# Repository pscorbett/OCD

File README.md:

# Over-Complicated Distortion (OCD)

This is a highly tweakable distortion pedal based around soft-clipping diodes in feedback.

## Controls
1. **Drive:** Adds gain to push the diodes into their non-linear region.
2. **Filter:** Crossmixes between Lowpass Filter and Highpass Filter. The 2nd-order Salley-key filter occurs before the clipping stage.
3. **Bias:** Adds a DC shift to the signal prior to the clipping stage. This can be used for asymmetric clipping as would occur in many tube and transistor Class-A amplifiers if they exceed their linear range.
4. **Symmetry:** Blends betweent the forward and reverse steering diodes in the feedback path. At higher gain values, the asymmetry will be diminished as the second set of (symmetric) clipping diodes is mixed in. This is done to achieve more extreme waveshaping than is possible with the resistance from the potentiometer limitng the steering current.
5. **Attenuvert:** This acts as an ouput control that affects only the clipped signal. In the CCW direction, the signal inverts.
6. **Mix:** Mixes between the dry and wet (distorted) signals. High distortion settings with low mix can simulate the crossover distortion produced by a Class B push-pull amplifier. Reversing the polarity results in a different flavor of crossover distortion.

Despite the name, this circuit has no association or deliberate simularities with other *OCD* distortion pedals.

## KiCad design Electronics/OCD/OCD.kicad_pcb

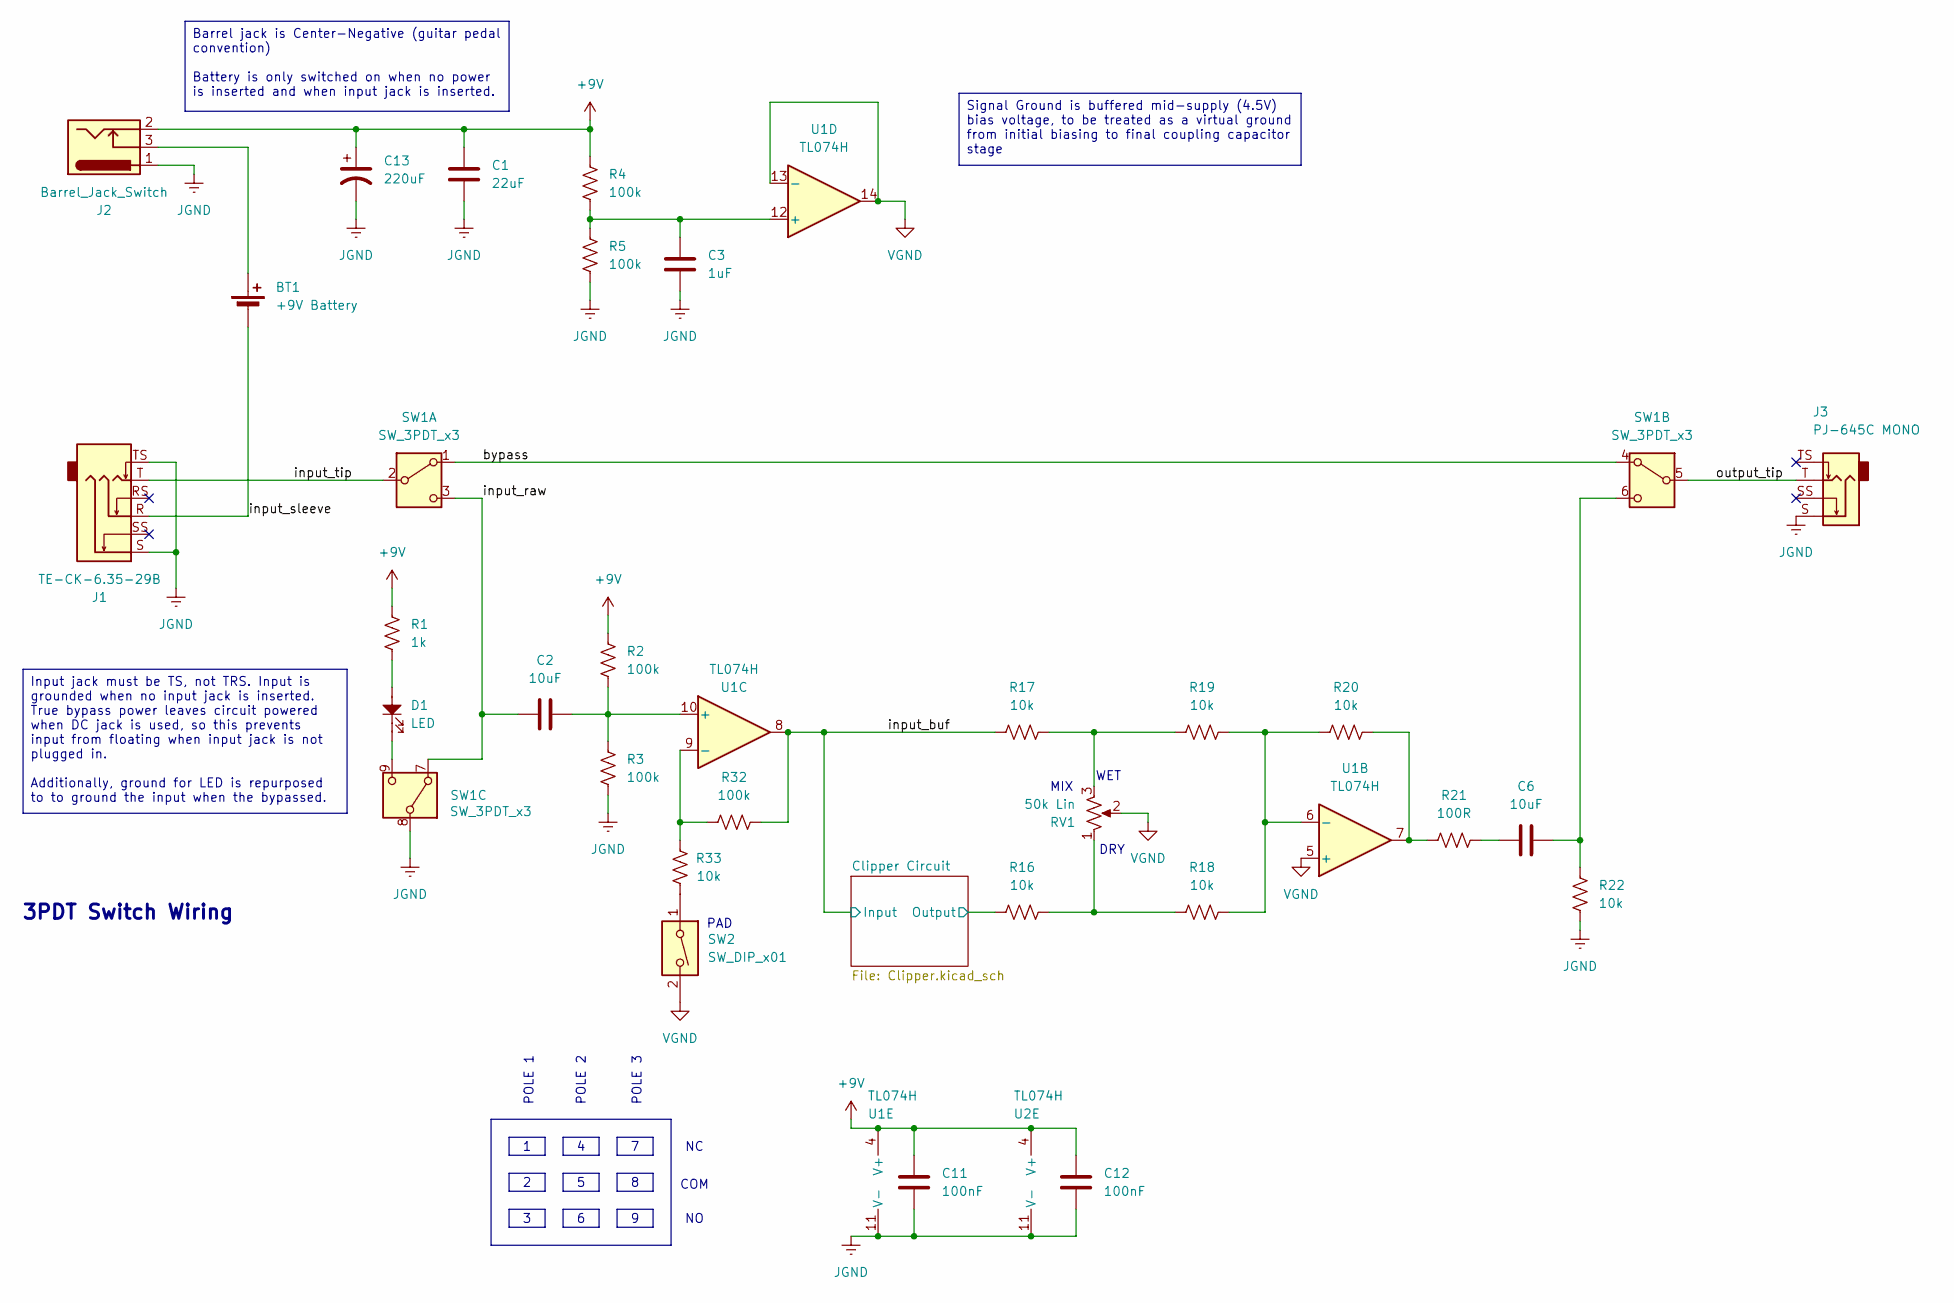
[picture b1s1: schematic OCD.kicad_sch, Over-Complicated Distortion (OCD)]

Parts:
BT1: +9V Battery; PinHeader_1x02_P2.54mm_Vertical; Part Number BH9VPC
C1: 22uF; C_0805_2012Metric; Part Number CL21A226MAQNNNE
C2, C6: 10uF; C_0805_2012Metric; Part Number GRM21BZ71E106KE15L
C3: 1uF; C_0805_2012Metric; Part Number CL21B105KBFNNNE
C11, C12: 100nF; C_0805_2012Metric; Part Number CL21B104KCFNNNE
C13: 220uF; CP_Elec_8x10; Part Number UUD1E221MNL1GS
D1: LED; LED_D5.0mm; Part Number PBS-24-302-N2 Red/Green LED
J1: TE-CK-6.35-29B; Part Number TE-PJ-645C
J2: Barrel_Jack_Switch; PinHeader_1x03_P2.54mm_Vertical; Part Number DC Power Bulkhead Jack 2.1mm
J3: PJ-645C MONO; PJ-644C MONO; Part Number PJ-645C MONO
R1: 1k; R_0805_2012Metric; Part Number 0805W8F1001T5E
R2, R3, R4, R5, R32: 100k; R_0805_2012Metric; Part Number 0805W8F1003T5E
R16, R17, R18, R19, R20, R22, R33: 10k; R_0805_2012Metric; Part Number 0805W8F1002T5E
R21: 100R; R_0805_2012Metric; Part Number 0805W8F1000T5E
RV1: 50k Lin; RV16AF-41; Part Number RV16106NO-OS15A00-B50K-060C
SW1: SW_3PDT_x3; PinHeader_1x09_P2.54mm_Vertical; Part Number PBS-24-302-N2 Red/Green LED
SW2: SW_DIP_x01; SW_DIP_SPSTx01_Slide_6.7x4.1mm_W8.61mm_P2.54mm_LowProfile; Part Number DSIC01LSGET
U1, U2: TL074H; SOIC-14_3.9x8.7mm_P1.27mm; Part Number TL074HIDR

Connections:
+9V: C1.1, C11.2, C12.2, C13.1, J2.2, R1.1, R2.1, R4.1, U1.4 (V+), U2.4 (V+); also elsewhere on the board
/Clipper Circuit/Output: R16.1; also elsewhere on the board
/bypass: SW1.1 (A), SW1.4 (A)
/input_buf: R17.1, R32.2, U1.8; also elsewhere on the board
/input_raw: C2.1, SW1.3 (C), SW1.7 (A)
/input_sleeve: BT1.2 (-), J1.R
/input_tip: J1.T, SW1.2 (B)
/output_tip: J3.T, SW1.5 (B)
JGND: C1.2, C3.2, C11.1, C12.1, C13.2, J1.S, J1.TS, J2.1, J3.S, R3.2, R5.2, R22.1, SW1.8 (B), U1.11 (V-), U2.11 (V-); also elsewhere on the board
unnamed: BT1.1 (+), J2.3
unnamed: C6.1, R21.2
unnamed: D1.2, R1.2
unnamed: R16.2, R18.1, RV1.1
unnamed: R17.2, R19.1, RV1.3
unnamed: R20.2, R21.1, U1.7
unnamed: R33.2, SW2.1
unnamed: C6.2, R22.2, SW1.6 (C)
unnamed: D1.1, SW1.9 (C)
unnamed: R18.2, R19.2, R20.1, U1.6 (-)
unnamed: C2.2, R2.2, R3.1, U1.10 (+)
unnamed: R32.1, R33.1, U1.9 (-)
unnamed: C3.1, R4.2, R5.1, U1.12 (+)
VGND: RV1.2, SW2.2, U1.5 (+), U1.13 (-), U1.14; also elsewhere on the board

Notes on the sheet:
PAD
POLE 1
COM
3PDT Switch Wiring
WET
DRY
MIX
POLE 2
POLE 3
Signal Ground is buffered mid-supply (4.5V) bias voltage, to be treated as a virtual ground from initial biasing to final coupling capacitor stage
Barrel jack is Center-Negative (guitar pedal convention) Battery is only switched on when no power is inserted and when input jack is inserted.
Input jack must be TS, not TRS. Input is grounded when no input jack is inserted. True bypass power leaves circuit powered when DC jack is used, so this prevents input from floating when input jack is not plugged in. Additionally, ground for LED is repurposed to to ground the input when the bypasse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

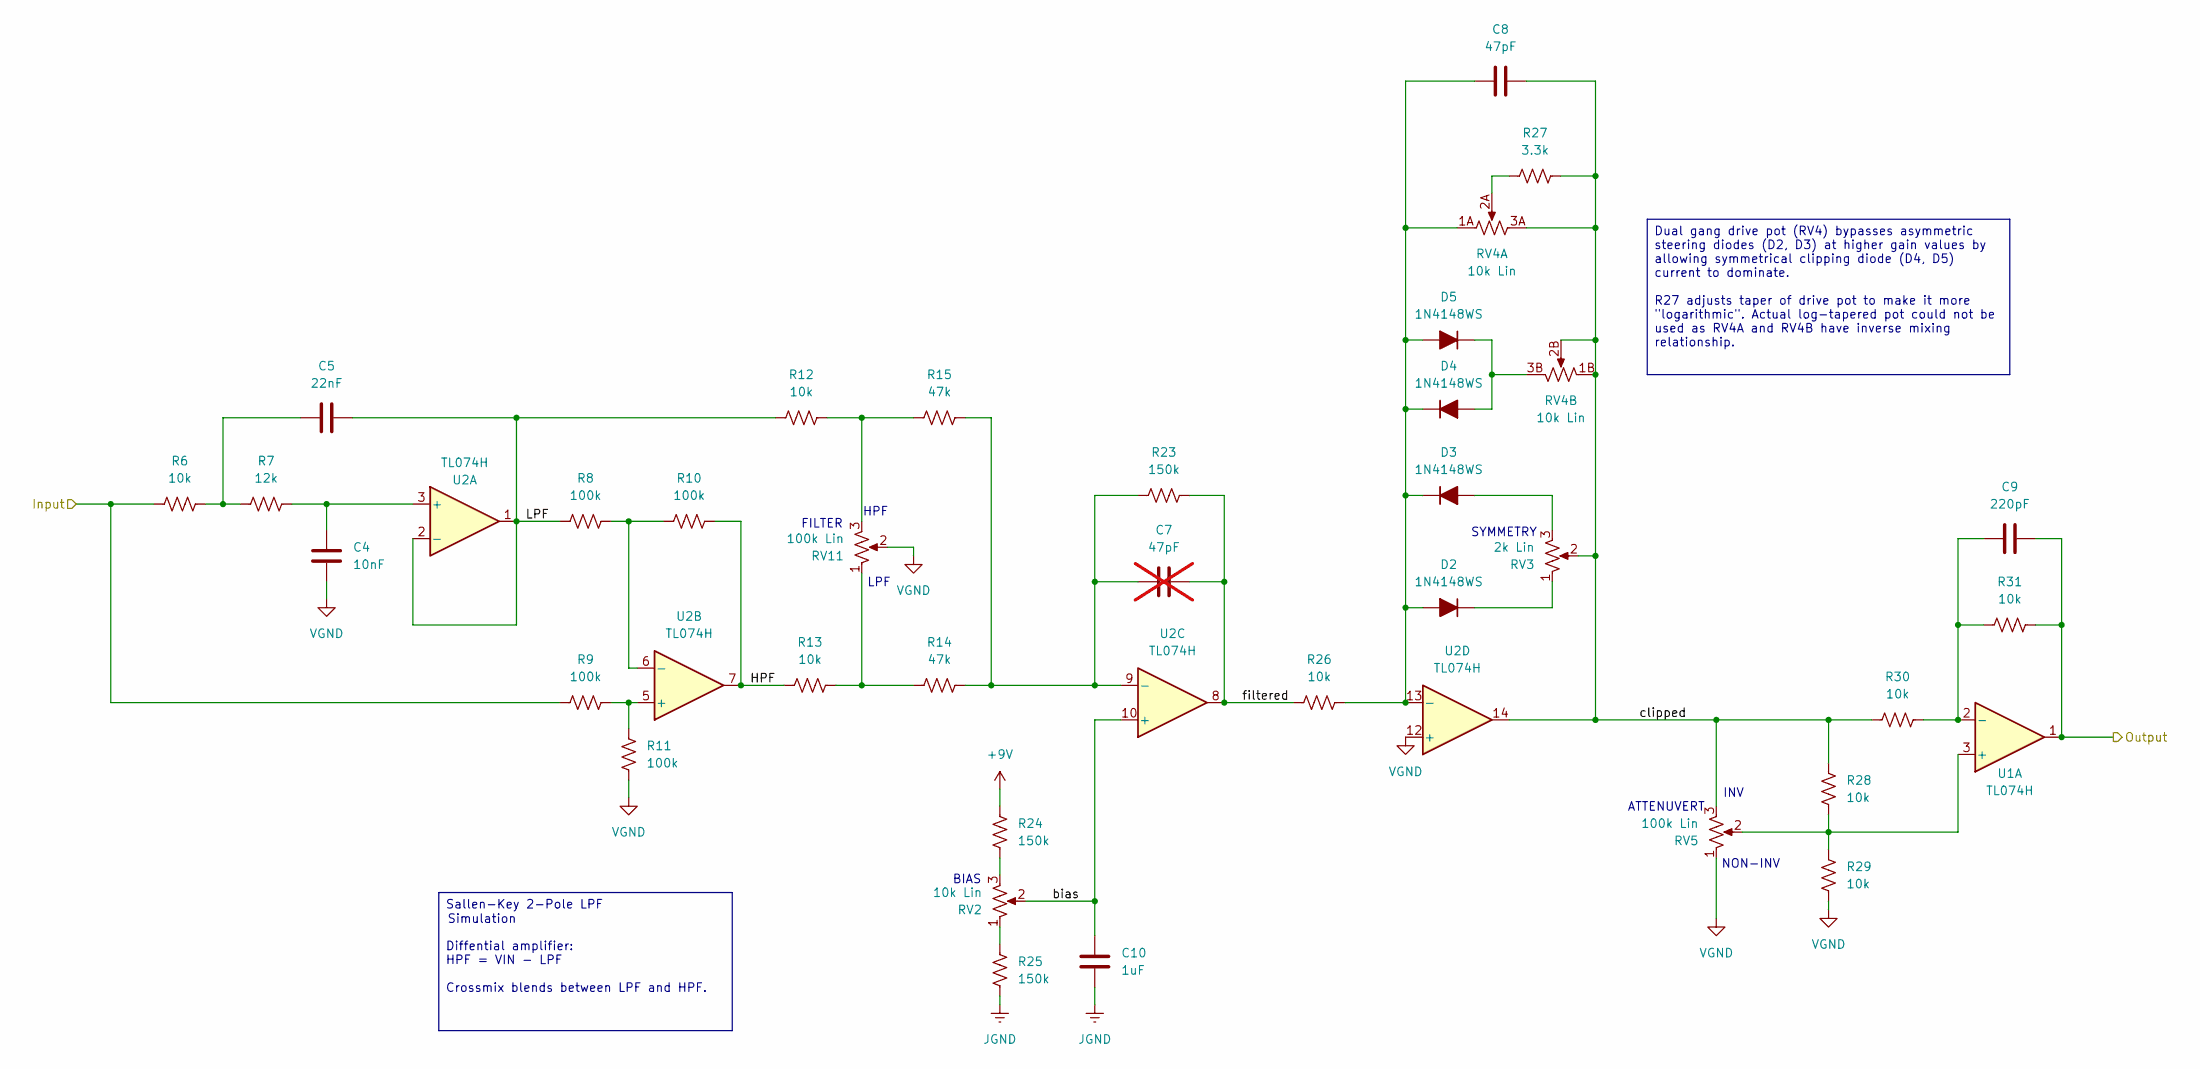
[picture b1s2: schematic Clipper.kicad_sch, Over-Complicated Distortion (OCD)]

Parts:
C4: 10nF; C_0805_2012Metric; Part Number GRM2195C1H103JA01D
C5: 22nF; C_0805_2012Metric; Part Number GRM21B5C1H223JA01L
C7: 47pF; C_0805_2012Metric; Part Number CL21C470JBANNNC; not fitted
C8: 47pF; C_0805_2012Metric; Part Number CL21C470JBANNNC
C9: 220pF; C_0805_2012Metric; Part Number CL21C221JBANNNC
C10: 1uF; C_0805_2012Metric; Part Number CL21B105KBFNNNE
D2, D3, D4, D5: 1N4148WS; D_SOD-323; Part Number 1N4148WS
R6, R12, R13, R26, R28, R29, R30, R31: 10k; R_0805_2012Metric; Part Number 0805W8F1002T5E
R7: 12k; R_0805_2012Metric; Part Number 0805W8F1202T5E
R8, R9, R10, R11: 100k; R_0805_2012Metric; Part Number 0805W8F1003T5E
R14, R15: 47k; R_0805_2012Metric; Part Number 0805W8F4702T5E
R23, R24, R25: 150k; R_0805_2012Metric; Part Number 0805W8F1503T5E
R27: 3.3k; R_0805_2012Metric; Part Number 0805W8F3301T5E
RV2: 10k Lin; RV16AF-41; Part Number RV16106NO-OS15A00-B10K-060C
RV3: 2k Lin; RV16AF-41; Part Number RV16AF-41-15R1-B2K
RV4: 10k Lin; RV16A10F-41-(L)R-XXX-3X(3); Part Number RV16106GO-0S15AO0-B10K-060
RV5, RV11: 100k Lin; RV16AF-41; Part Number RV16106NO-OS15A00-B100K-060C
U1, U2: TL074H; SOIC-14_3.9x8.7mm_P1.27mm; Part Number TL074HIDR

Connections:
+9V: R24.2; also elsewhere on the board
/Clipper Circuit/HPF: R10.2, R13.1, U2.7
/Clipper Circuit/LPF: C5.1, R8.1, R12.1, U2.1, U2.2 (-)
/Clipper Circuit/Output: C9.1, R31.1, U1.1; also elsewhere on the board
/Clipper Circuit/bias: C10.1, RV2.2, U2.10 (+)
/Clipper Circuit/clipped: C8.1, R27.2, R28.2, R30.2, RV3.2, RV4.1B, RV4.2B, RV4.3A, RV5.3, U2.14
/Clipper Circuit/filtered: C7.1, R23.2, R26.1, U2.8
/input_buf: R6.1, R9.1; also elsewhere on the board
JGND: C10.2, R25.1; also elsewhere on the board
unnamed: C5.2, R6.2, R7.1
unnamed: C8.2, D2.2 (A), D3.1 (K), D4.1 (K), D5.2 (A), R26.2, RV4.1A, U2.13 (-)
unnamed: D2.1 (K), RV3.1
unnamed: D3.2 (A), RV3.3
unnamed: D4.2 (A), D5.1 (K), RV4.3B
unnamed: R12.2, R15.1, RV11.3
unnamed: R13.2, R14.1, RV11.1
unnamed: R24.1, RV2.3
unnamed: R25.2, RV2.1
unnamed: R27.1, RV4.2A
unnamed: R28.1, R29.2, RV5.2, U1.3 (+)
unnamed: C9.2, R30.1, R31.2, U1.2 (-)
unnamed: C4.2, R7.2, U2.3 (+)
unnamed: R9.2, R11.2, U2.5 (+)
unnamed: R8.2, R10.1, U2.6 (-)
unnamed: C7.2, R14.2, R15.2, R23.1, U2.9 (-)
VGND: C4.1, R11.1, R29.1, RV5.1, RV11.2, U2.12 (+); also elsewhere on the board

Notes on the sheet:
ATTENUVERT
FILTER
BIAS
HPF
INV
LPF
NON-INV
SYMMETRY
Simulation
Sallen-Key 2-Pole LPF Diffential amplifier: HPF = VIN - LPF Crossmix blends between LPF and HPF.
Dual gang drive pot (RV4) bypasses asymmetric steering diodes (D2, D3) at higher gain values by allowing symmetrical clipping diode (D4, D5) current to dominate. R27 adjusts taper of drive pot to make it more "logarithmic". Actual log-tapered pot could not be used as RV4A and RV4B have inverse mixi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

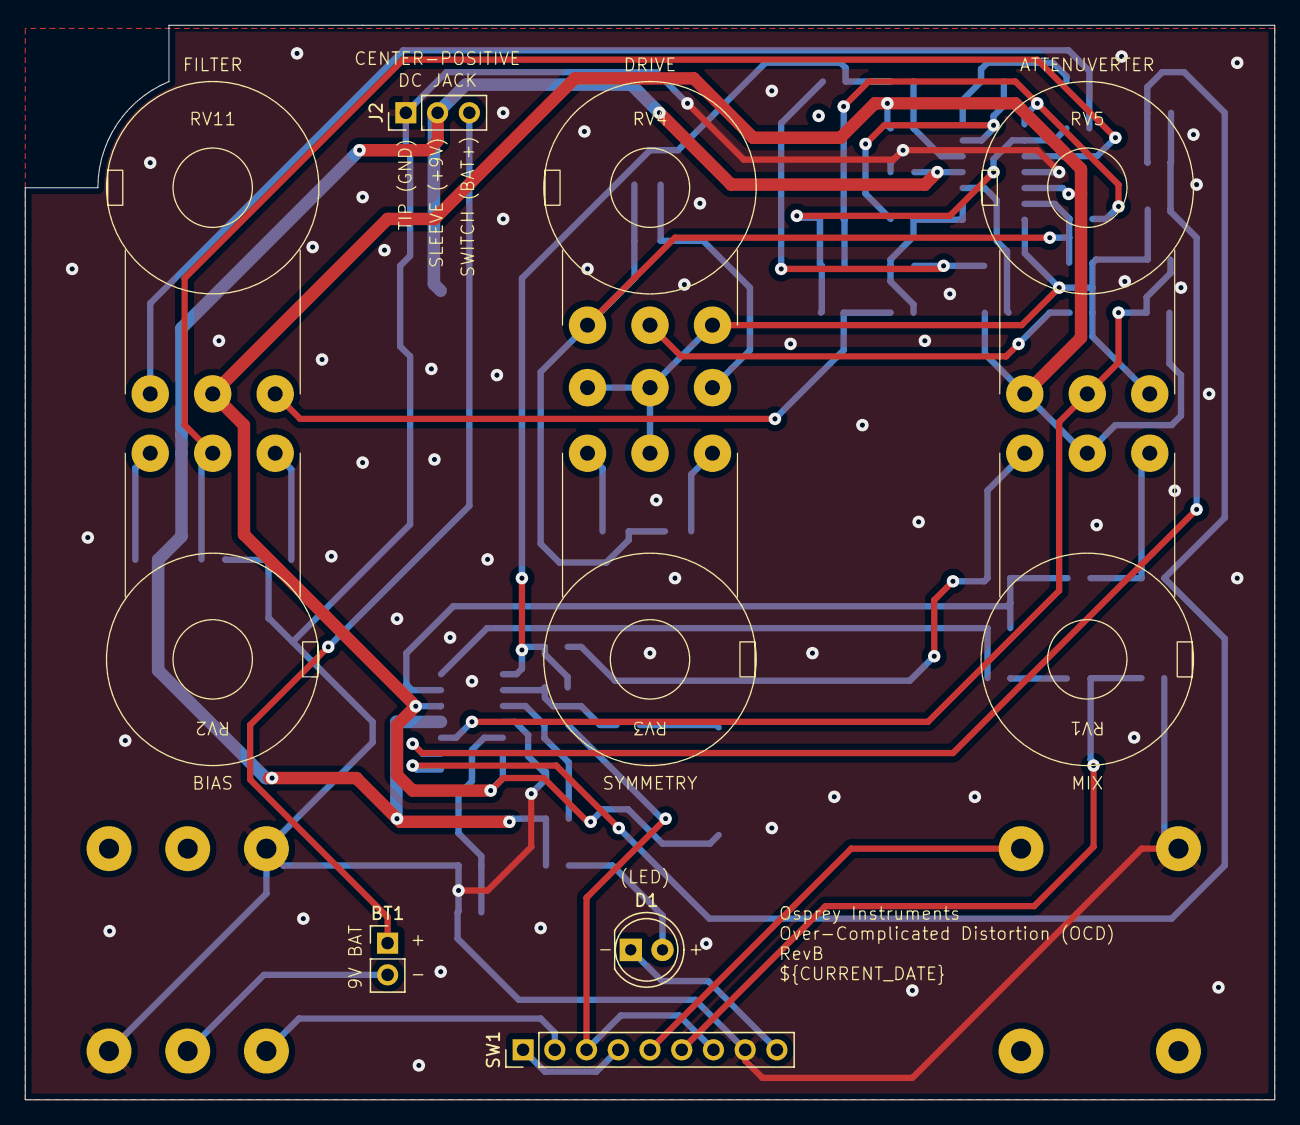
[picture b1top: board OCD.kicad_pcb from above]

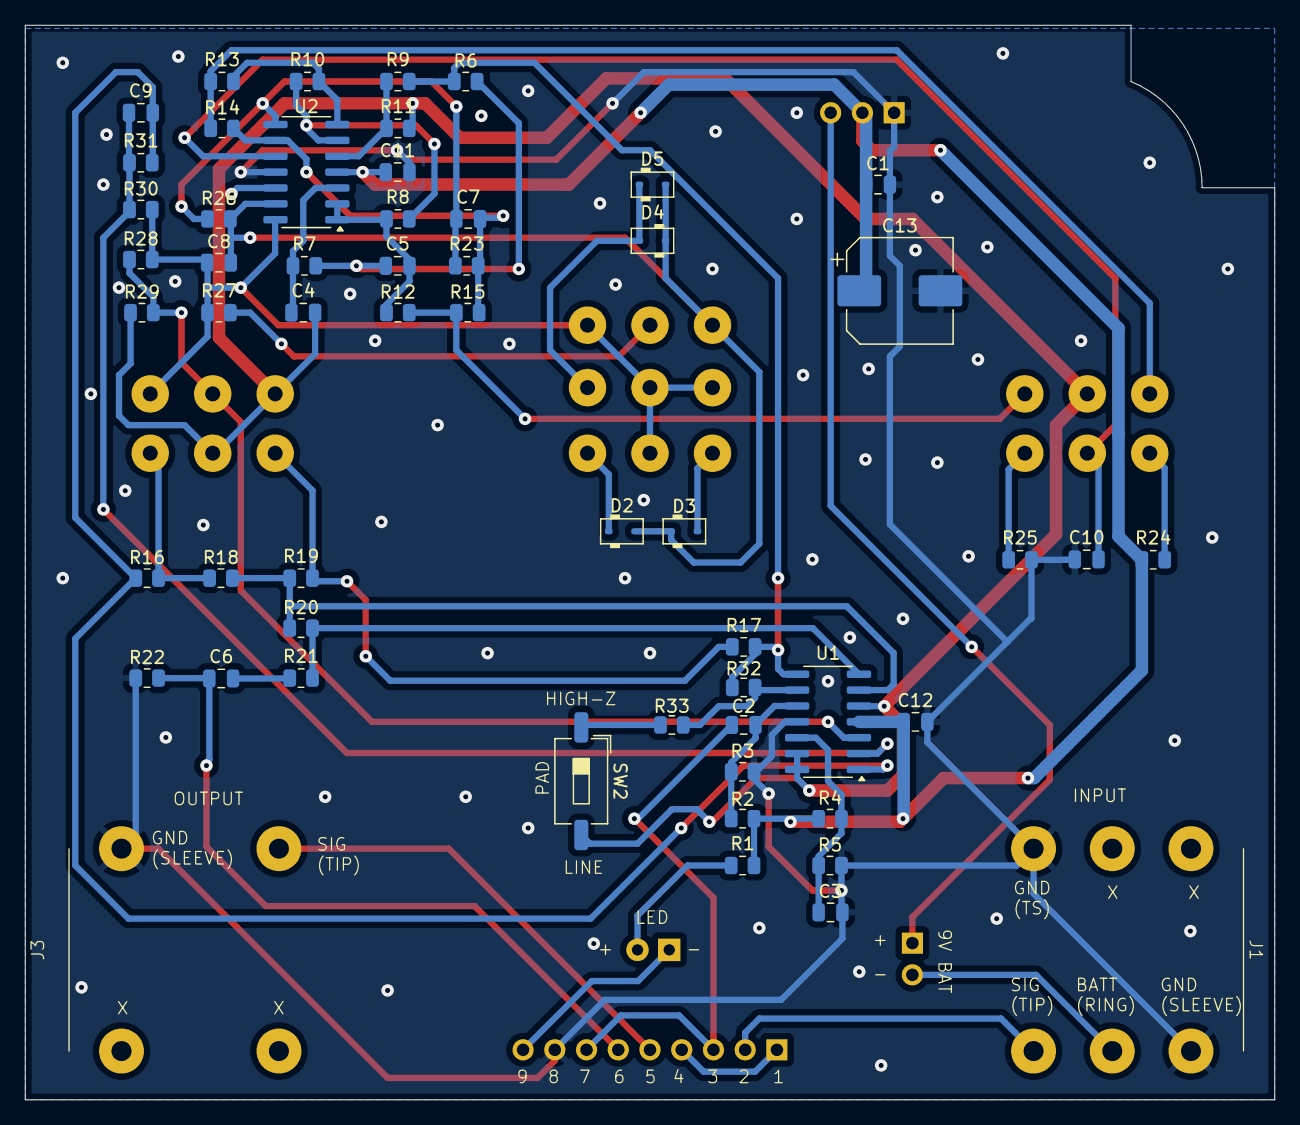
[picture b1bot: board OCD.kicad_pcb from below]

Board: 2 copper layers, 100.0 x 86.0 mm, 65 parts (55 on the bottom side), 44 nets.

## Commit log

2025-09-25 silkscreen pdf and schematic update to center-negative
2025-09-30 RevA release
2025-10-27 RevB release. Corrected opamp orientation, added pad switch
